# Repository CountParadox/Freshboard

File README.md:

# Freshboard
6 Key Macro Keypad using RP2040 Zero

http://www.keyboard-layout-editor.com/##@_name=Freshboard&author=VK2EVA%3B&@_a:0%3B&=1%0A%0A%0A%0A0%0A0%0A%0A%0AKC%2F_1&=2%0A%0A%0A%0A0%0A1%0A%0A%0AKC%2F_2&=3%0A%0A%0A%0A0%0A2%0A%0A%0AKC%2F_3&=4%0A%0A%0A%0A0%0A3%0A%0A%0AKC%2F_4&=5%0A%0A%0A%0A0%0A4%0A%0A%0AKC%2F_5&=6%0A%0A%0A%0A0%0A5%0A%0A%0AKC%2F_6

You will need: 

- PCC
- RP2040 Zero
- Kailh Hotswap sockets
- MX Style Switches
- Diodes? if your PCB doesnt have them

RP2040 Zero: https://www.aliexpress.com/item/1005004288978233.html
Sockets: https://www.aliexpress.com/item/1005003704619399.html or other
Switches: https://www.aliexpress.com/item/1005004285423123.html or other

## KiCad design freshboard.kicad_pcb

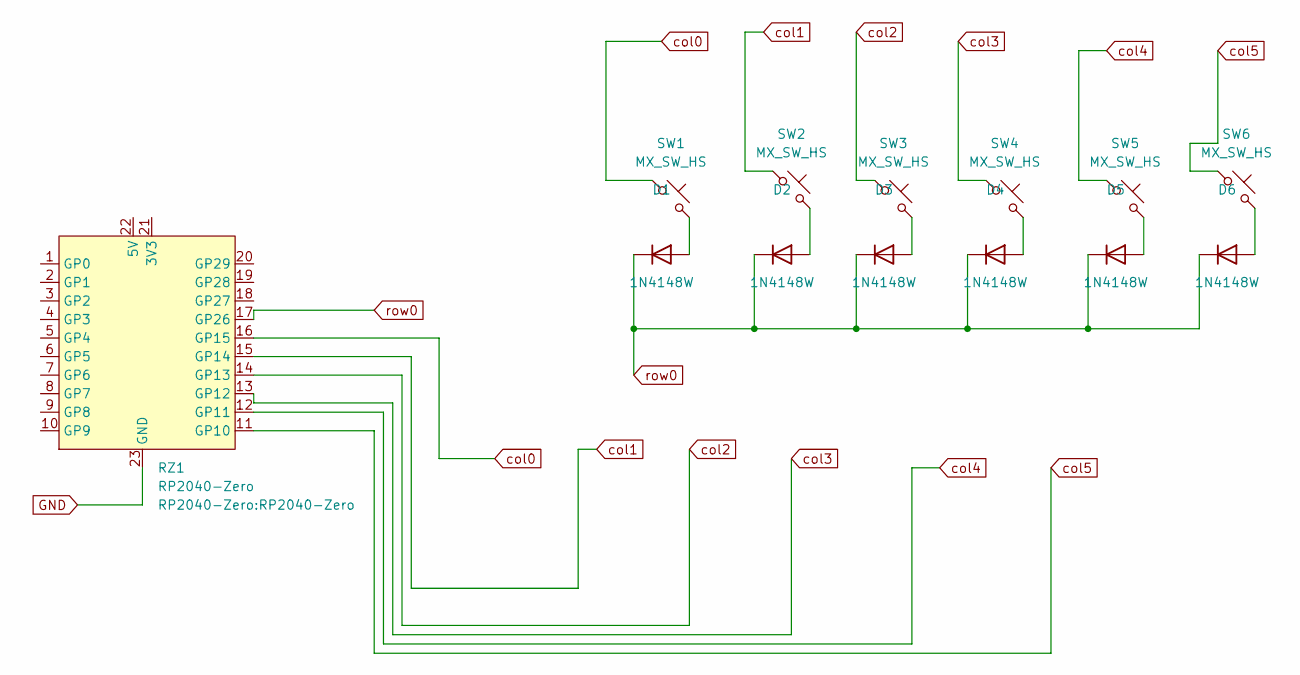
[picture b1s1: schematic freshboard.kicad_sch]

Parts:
D1, D2, D3, D4, D5, D6: 1N4148W; D_SOD-123
RZ1: RP2040-Zero
SW1, SW2, SW3, SW4, SW5, SW6: MX_SW_HS; SW_MX_HS_1u

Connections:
GND: RZ1.23 (GND)
unnamed: D1.2 (A), SW1.2
unnamed: D2.2 (A), SW2.2
unnamed: D3.2 (A), SW3.2
unnamed: D4.2 (A), SW4.2
unnamed: D5.2 (A), SW5.2
unnamed: D6.2 (A), SW6.2
col0: RZ1.16 (GP15), SW1.1
col1: RZ1.15 (GP14), SW2.1
col2: RZ1.14 (GP13), SW3.1
col3: RZ1.13 (GP12), SW4.1
col4: RZ1.12 (GP11), SW5.1
col5: RZ1.11 (GP10), SW6.1
row0: D1.1 (K), D2.1 (K), D3.1 (K), D4.1 (K), D5.1 (K), D6.1 (K), RZ1.17 (GP26)

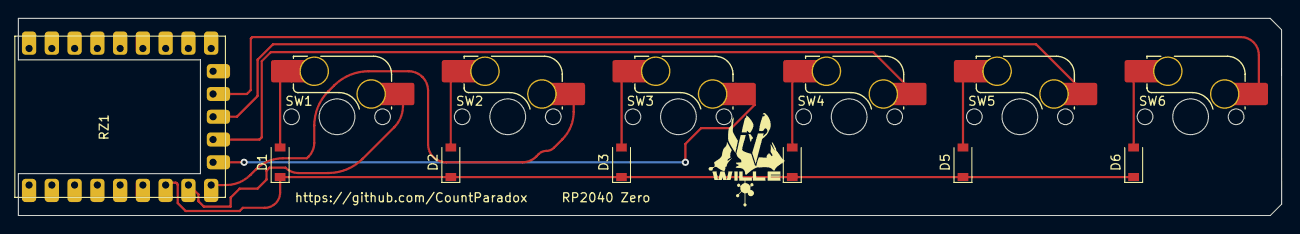
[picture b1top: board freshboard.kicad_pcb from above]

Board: 2 copper layers, 141.0 x 22.0 mm, 13 parts (0 on the bottom side), 13 nets.

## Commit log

2022-10-12 initial push
2022-10-12 added firmware
2022-10-12 add case files (top, bottom, plate and fusion f3z file)
